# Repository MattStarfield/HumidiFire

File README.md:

# HumidiFire
A water vapor based fireplace simulator

### Table of Contents
* [Documentation](#Documentation)
* [Hardware](#Hardware)
* [Firmware](#Firmware)
* [Software](#Software)
---

## Documentation

## Hardware
* [Bill of Materials](https://docs.google.com/spreadsheets/d/1JZTtaZDqRExDhAQ4nWuzvwM8wr-2eBfdn1ZWpzmeVy4/edit#gid=0)

## Firmware

## Software

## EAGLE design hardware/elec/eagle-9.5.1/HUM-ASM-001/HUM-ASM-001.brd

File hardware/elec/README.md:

### Hardware > Electrical Design
Contains PCB and electronics design files including:

Eagle CAD Project files:
- [ ] Schematic `.sch`
- [ ] PCB Layout `.brd`
- [ ] Library Components `.lbr`
- [ ] Eagle Project File `eagle.epf`

Exported files:
- [ ] Schematic PDF `.pdf`
- [ ] PCB image Render `.png`
- [ ] Gerber files `.zip`

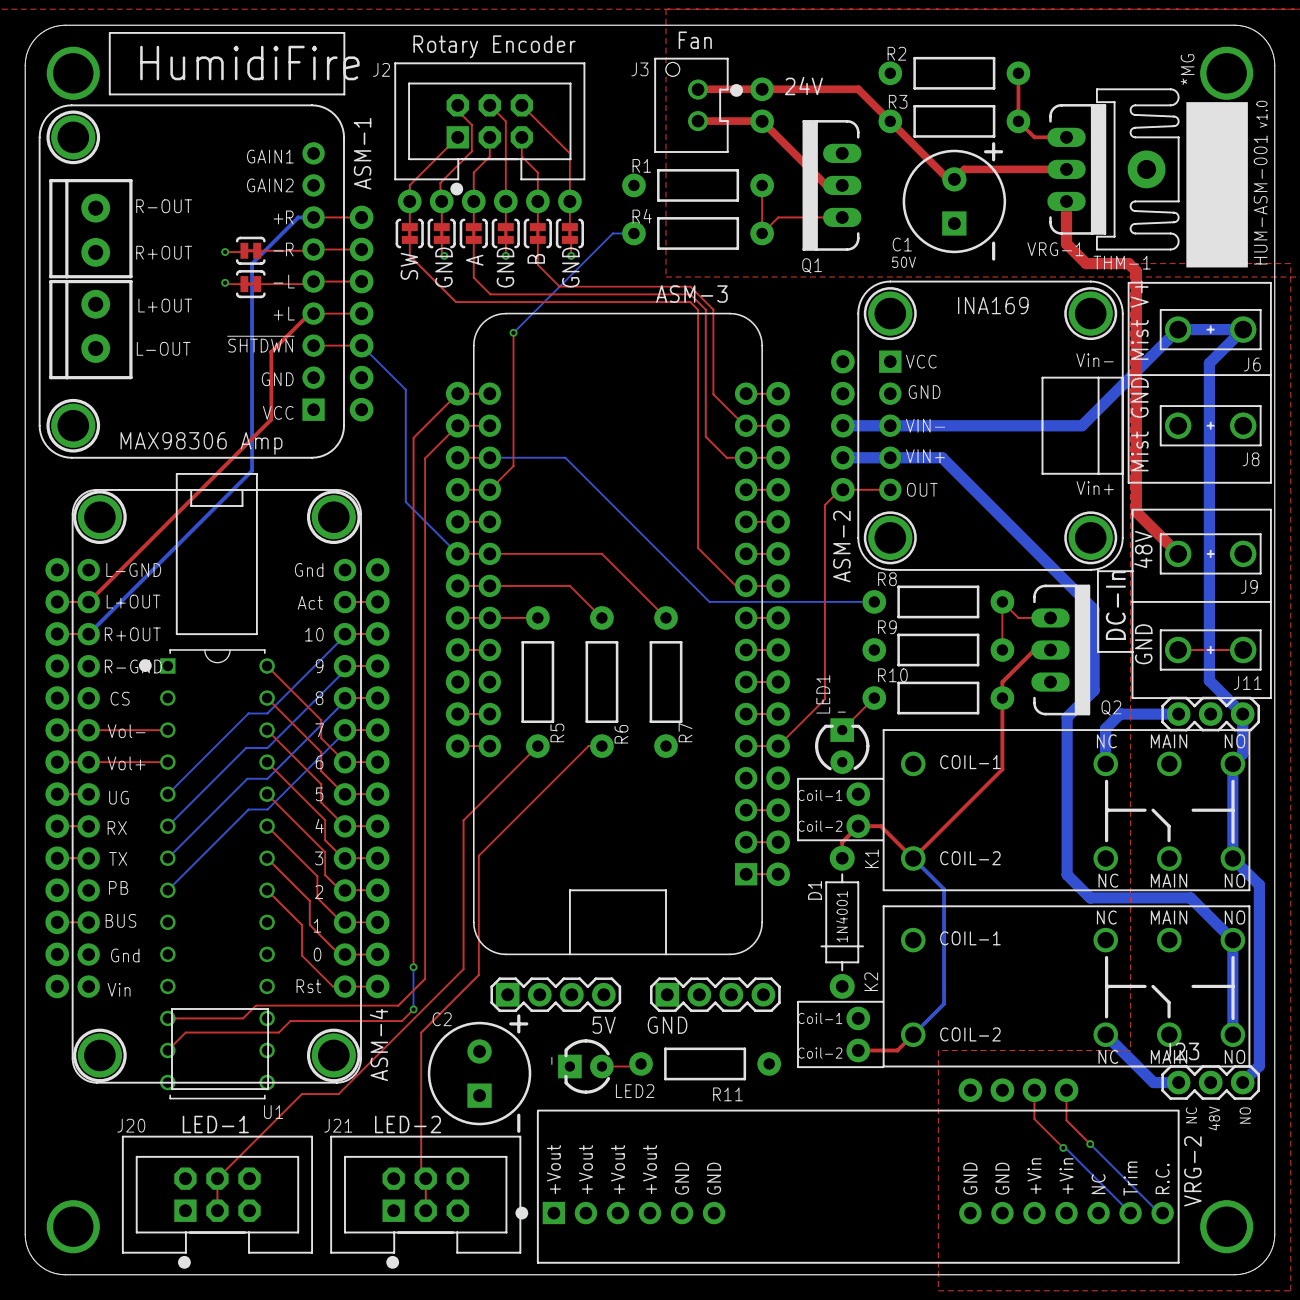
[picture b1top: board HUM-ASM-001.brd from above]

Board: 2 copper layers, 99.1 x 99.1 mm, 63 parts (0 on the bottom side), 74 nets.

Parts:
ASM-1: ASM_ADAFRUIT_MAX98306_AMP_MOUNTING_HOLES
ASM-2: ASM_ADAFRUIT_INA169_MOUNTING_HOLES
ASM-3: Feather Bluefruit 32u4; ASM_ADAFRUIT_FEATHER_BLUEFRUIT
ASM-4: ASM_ADAFRUIT_SOUND_FX_BOARD
C1, C2: 100uF, 50V; CAP_E-035X080
D1: 1N4001; DIODE-1N4001
J1: 1X06_NO_SILK
J2, J20, J21: 75869-131LF; 2X3-SHROUDED
J3: B2B-XH-AM(LF)(SN); JST-2-PTH-VERT_XH
J4, J14, J19: 1X02_NO_SILK
J5: 1X07_NO_SILK
J6, J8, J9, J11: TE_1217861-1
J7: 1X05_NO_SILK
J10, J23: 1X03
J12: 1X12_NO_SILK
J13: 1X16_NO_SILK
J15, J16: 1X14_NO_SILK
J17, J18: 1X04
J22: 1X04_NO_SILK_ALL_ROUND
JP1, JP2, JP3, JP4, JP5, JP6, JP7, JP8: CON_JUMPER_PAD-2-NC_BY_TRACE; PAD-JUMPER-2-NC_BY_TRACE_YES_SILK
K1, K2: 7-1393239-7; RELAY_TE_7-1393239-7
LED1, LED2: 3mm Green; LED3MM
MH1, MH2, MH3, MH4: TOOLING_HOLE_0.125_IN_HORSESHOE
Q1, Q2: IRLB8721PBF; TO-220-VERTICAL
R1, R9: 10k; AXIAL-0.4
R2: 4k, 1%; AXIAL-0.4
R3: 220; AXIAL-0.4
R4, R5, R6, R8, R10, R11: 100; AXIAL-0.4
R7: 1k; AXIAL-0.4
THM-1: V5629W220; SK95-2M3
U1: MCP23017-E/SP; DIP787W45P254L3556H508Q28
VRG-1: LM317; TO-220-VERTICAL
VRG-2: NID100-5; VRG_NID100-X

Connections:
3V: ASM-3.3V3, J13.2
5V: ASM-1.1, ASM-2.1, ASM-3.USB/VBUS, ASM-4.28, C2.+, D1.C, J5.7, J7.5, J12.3, J14.1, J15.1, J17.1, J17.2, J17.3, J17.4, J19.1, J20.1, J20.2, J21.1, J21.2, K1.COIL-1, K2.COIL-1, LED1.A, R11.P$1, U1.9, U1.18, VRG-2.P$1, VRG-2.P$2, VRG-2.P$3, VRG-2.P$4
24V: C1.+, J3.1, J4.1, R3.P$2, VRG-1.P2
48V: J9.1, J9.2, J10.2, J22.3, J22.4, J23.2, K1.MAIN-1, K1.MAIN-2, K2.MAIN-1, K2.MAIN-2, VRG-1.P3, VRG-2.P$9, VRG-2.P$10
!AMP-SHDN: ASM-1.3, ASM-3.D10, J5.5, J12.7, R7.P$2
ADJ: R2.P$2, R3.P$1, VRG-1.P1
CRNT-MON: ASM-2.5, ASM-3.A0, J7.1, J13.5
DFU: ASM-3.DFU, J13.16
ENCODER-A: ASM-3.RX0, J13.14, JP5.1
ENCODER-B: ASM-3.TX1, J13.15, JP7.1
ENCODER-SW: ASM-3.A5, J13.10, JP3.1
FAN-CTRL: ASM-3.D6, J12.9, R4.P$1
GND: ASM-1.2, ASM-2.2, ASM-3.GND@4, ASM-4.14, ASM-4.15, ASM-4.18, ASM-4.27, C1.-, C2.-, J5.6, J7.4, J8.1, J8.2, J11.1, J11.2, J13.4, J15.2, J15.11, J15.14, J16.14, J18.1, J18.2, J18.3, J18.4, J20.5, J20.6, J21.5, J21.6, JP1.1, JP2.1, JP4.1, JP6.1, JP8.1, LED2.K, Q1.P3, Q2.P3, R1.P$2, R2.P$1, R7.P$1, R9.P$2, U1.10, U1.15, U1.16, U1.17, VRG-2.P$5, VRG-2.P$6, VRG-2.P$7, VRG-2.P$8
I2C-SCL: ASM-3.SCL, J12.11, U1.12
I2C-SDA: ASM-3.SDA, J12.12, U1.13
K1-NC: J10.1, K1.NC-1
K2-NC: J23.1, K2.NC-2
LED1-DATA: ASM-3.D12, J12.5, R5.P$2
LED2-DATA: ASM-3.D11, J12.6, R6.P$1
MIST-CTRL: ASM-3.D5, J12.10, R8.P$1
MIST-VIN: ASM-2.3, J6.1, J6.2, J7.3, J10.3, J23.3, K1.NO-1, K1.NO-2
unnamed: ASM-3.!RESET, J13.1
unnamed: ASM-3.AREF, J13.3
unnamed: ASM-3.A1, J13.6
unnamed: ASM-3.A2, J13.7
unnamed: ASM-3.A3, J13.8
unnamed: ASM-3.A4, J13.9
unnamed: J20.3, J20.4, R5.P$1
unnamed: D1.A, J14.2, J19.2, K1.COIL-2, K2.COIL-2, Q2.P2, R10.P$1
unnamed: Q2.P1, R8.P$2, R9.P$1
unnamed: J3.2, J4.2, Q1.P2
unnamed: LED1.K, R10.P$2
unnamed: ASM-1.5, J5.3, JP2.2
unnamed: ASM-1.6, J5.2, JP1.2
unnamed: ASM-2.4, J7.2, K2.NO-1, K2.NO-2
unnamed: Q1.P1, R1.P$1, R4.P$2
unnamed: J1.1, J2.1, JP3.2
unnamed: LED2.A, R11.P$2
unnamed: ASM-3.D9, J12.8
unnamed: J1.2, J2.2, JP4.2
unnamed: J1.3, J2.3, JP5.2
unnamed: ASM-3.D13, J12.4
unnamed: ASM-3.EN, J12.2
unnamed: ASM-4.13, J16.13
unnamed: J22.1, VRG-2.P$13
unnamed: J22.2, VRG-2.P$12
unnamed: ASM-4.24, J15.5
unnamed: ASM-4.23, J15.6
unnamed: ASM-4.22, J15.7
unnamed: J1.4, J2.4, JP6.2
unnamed: J1.5, J2.5, JP7.2
unnamed: J1.6, J2.6, JP8.2
unnamed: J21.3, J21.4, R6.P$2
SFX-0: ASM-4.2, J16.2, U1.22
SFX-1: ASM-4.3, J16.3, U1.23
SFX-2: ASM-4.4, J16.4, U1.24
SFX-3: ASM-4.5, J16.5, U1.25
SFX-4: ASM-4.6, J16.6, U1.26
SFX-5: ASM-4.7, J16.7, U1.27
SFX-6: ASM-4.8, J16.8, U1.28
SFX-7: ASM-4.9, J16.9, U1.8
SFX-8: ASM-4.10, J16.10, U1.7
SFX-9: ASM-4.11, J16.11, U1.6
SFX-10: ASM-4.12, J16.12, U1.5
SFX-LOUT: ASM-1.4, ASM-4.16, J5.4, J15.13
SFX-ROUT: ASM-1.7, ASM-4.17, J5.1, J15.12
SFX-RST: ASM-4.1, J16.1, U1.21
SFX-VOL-N: ASM-4.20, J15.9, U1.3
SFX-VOL-P: ASM-4.21, J15.8, U1.4
SPI-MISO: ASM-3.MISO, J13.13
SPI-MOSI: ASM-3.MOSI, J13.12
SPI-SCK: ASM-3.SCK, J13.11
USB/VBUS: ASM-4.26, J15.3
VBAT: ASM-3.VBAT, J12.1

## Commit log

2019-11-03 * draft lid cut out tester
2019-11-03 * minor update
2019-11-06 * added Bill of Materials
2019-11-09 * added vent deflector and floor register to lid cut out
2019-11-09 * moved cross flow fan inlet slit back from the fan body edge
2019-11-09 * added 24V Power Supply datasheet
2019-11-09 * initial draft firmware commit
2019-11-10 * added BLE Connect capability * Fan control via BLE (PWM range is not linear to fan speed)
2019-11-10 * - Rotary Encoder fan speed control * - Bluefruit Connect App fan, mist, and mode control
2019-11-14 * - collected and syncronized display updates of BLE & Serial Montior for settings changes at the end of loop() with settingsUpdate flag * - added modeToString() function to print mode names * - adde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
2019-11-14 * added TODO item
2019-11-15 * - added NeoPixel functionality
2019-11-16 * Added I2C expander code, but it isn't working yet and the loop code is runnig very slowly now. Needs debugging!
2019-11-21 * - Added campfire wav file * - Updated NUM_PIXELS to 31 * - Moved to Feather 32u4 * - Feather M0 has NO EEPROM memory!! * - Feather M0 isn't compatible with <Adafruit_MCP23008.h> I2C Expander library
2019-11-21 * ignored raw collection of WAV files - commit only after refined and edited
2019-11-28 - Upgraded to MCP23017 I2C 16 I/O Expander Library
2019-11-30 * - Added Current Monitor * - Upgraded to MCP23017 I2C 16 I/O Expander Library
2019-11-30 * updated lid plate for component placement in hole cut through bin lid
2019-11-30 * Updated zip tie holes for wider straps, made rectangular * moved fan, vent deflector, and floor vent back 0.5" * Corrected floor vent width * changed lid shelf corner radius to 2 cm
2019-11-30 * Added breadboard pass-through to back panel * reduced depth by 1 in
2019-12-01 * added speaker mount holes and moved AC Inlet alongside corss flow fan
2019-12-03 * updates to speaker grill, fan grill, ac inlet mounting holes
2019-12-04 * New shorter enclosure with 1/4" material * wall cut out for fan motor penetration * Fan mounted to base of enclosure * speakers on both sides, speaker profiles added for clearance
2019-12-04 * - Added Mister Relay control to Pin 5
2019-12-05 * Updated default PWM rate and step for Fan control
2019-12-05 * added PCB Floorplan
2019-12-07 * started PCB schematic
2019-12-10 * added more footprints to library and parts to schematic
2019-12-11 * finished building pcb library parts * added one of each part to schematic * added Power and Audio pages to schematic
2019-12-13 * Updated rotary encoder pin connections for Bourns encoder. * Rotation is now Interrupt based * Button press is now polling based
2019-12-14 * Added control for Amp Shutdown pin
2019-12-14 * Major progress on schematic
2019-12-14 * schematic complete
2019-12-14 * PCB component placement complete
2019-12-14 * Removed unneeded components (Breakout connectors and Jumpers) * Laid 5V and GND planes
2019-12-15 * pre-routed PCB
2019-12-15 * PCB 48V side routed
2019-12-15 * PCB Route complete
2019-12-16 * Fixed crash / recovery inconsistency * Pre silk screen clean up
2019-12-16 * Normalized Text for Names and Values
2019-12-16 * PCB Silk cleanup completed
2019-12-16 * Final PCB v1.0 edits * Exported Gerber files and send to fab
2019-12-16 * cleaned up folder * added PCB CAD image
2019-12-16 * corrected PCBway Gerber rejection * unchecked "Negative Image" for Soldermask layers in Eagle CAM processor
2019-12-18 * renamed Gerber versions
2019-12-18 * added PCB render to enclosure design * added PCB standoff markers * flipped fan motor side panel cutout so laser cut burns will be hidden inside enclosure * added Encoder panel mount cut outs and s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
2019-12-19 * New enclosure version * Fan Filter Grill * LED cable cutouts * Outlines made into guides
2019-12-19 * added press-fit fan filter spacers * added speaker spacer and backer supports
2019-12-19 * tightened up Fan Filter Grill spacer press-fit
2019-12-19 * Updated Encoder Backing support and Spacer * Added cut holes for PCB standoffs (for option to use screws)
2019-12-19 * positioning adjustments after testing prototype * Major updates to lid shelf * updated enclosure box for hinged lid
2019-12-20 * another round of minor enclosure and lid improvements based on last cut and test * Back mist visor elongated to become leg for bottom of lid
2019-12-21 * Moved to 3 visor approach with LEDs in Front and Mid * added vapor exhaust vent hole patterns * re-added LED cable pass through cut outs * added bottle holder designs
2019-12-21 * minor updates (not sure what)
2019-12-21 * designed jug support
2019-12-21 * moved back jug support back 0.25" * cleaned up file layer organization
2019-12-21 * raised jug support 1" to keep water line at 2.7" for float switch
2019-12-21 * updated size of hinge cut outs
2019-12-22 * Added Faux Rock Stencils * Added Mister wire passthrough Shelf Lid * Back Visor now has squared corners * Minor updates to Jug Spinte Support * Narrowed Bottle holder slots for tighter fit
2019-12-22 * Added cut lines to allow space to grip filter for removal
2019-12-22 * Updated file name
2019-12-22 * Cleaned up file layer organization
2019-12-23 * widened Bottle Holder hole * added pry-open slots to box sides
2019-12-23 * Updated Pinouts to reflect PCB wiring changes
2019-12-24 * Changed Back visor to 8" taller * Added notes to remove front vent and narrow back vent
2019-12-25 * pre-FSM model * now running 2 strips of LEDs * Sound & Volume control not tested / confirmed
2019-12-25 * ready to test new FSM model firmware, but having compile troubles. says BluefruitSetup.ino is not found, but it's in the folder
2019-12-25 * v1.0 - finite state machine model * added LOW_WATER monitor state * finalized LED scene, fan speed, and start up sequence
2020-01-03 * uploaded images
2020-01-27 * added libraries to repo
2020-01-27 * removed old unused library
